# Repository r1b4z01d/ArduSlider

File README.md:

*ArduSlider
** Arduino:
*** API:
The arduino expects each api call to consist of a letter (flag), set of numbers and a charige return. Example: B1000/n
In Flags: 
	T: Length of session in milliseconds
		T60000/n
	S: Sutter speed in milliseconds 
		S1000/n
	B: Length of time the cammera takes to save the image and clear it's buffer in milliseconds.
		B3000/n
	D: Distance of travel for the session in mm
		D1000/n
	R: Boolen trigger to start/stop the session.
		R1/n
	A: Request a full refresh of all parameters
		A/n 

Out:

  sendData("T",String(msOfCapture));
  sendData("P",String(photo));
  sendData("C",String(numPhotos));
  sendData("R",String(isRunning));
  sendData("S",String(shutterSpeed));
  sendData("B",String(bufferClear));
  sendData("D",String(mmOfTravel));
  sendData("L",String(totalSteps));

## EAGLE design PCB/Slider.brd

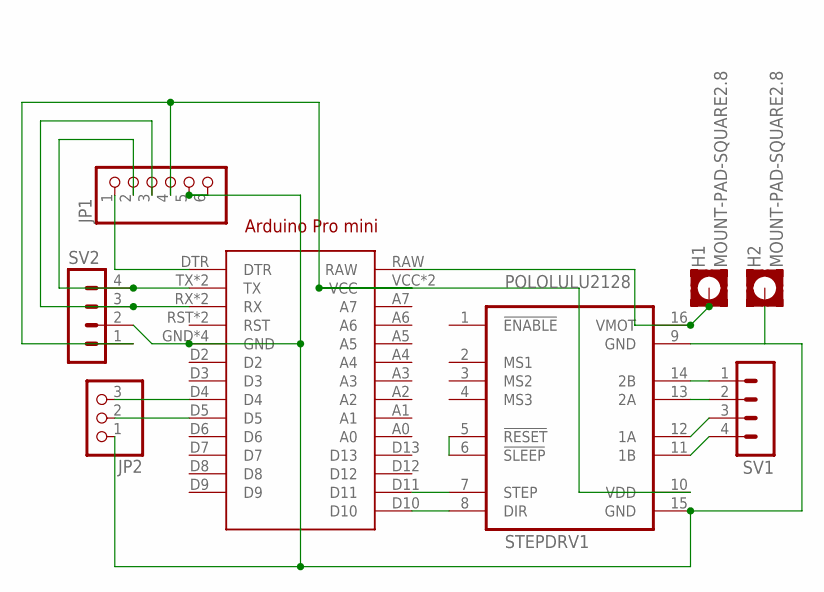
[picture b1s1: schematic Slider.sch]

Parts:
ARDUINO1: ARDUINO_PRO_MINI
H1, H2: MOUNT-PAD-SQUARE2.8; 2,8-PAD-SQUARE
JP1: PINHD-1X6; 1X06
JP2: PINHD-1X3CB; 1X03-CLEANBIG
STEPDRV1: POLOLULU2128
SV1, SV2: MA04-1

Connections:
unnamed: ARDUINO1.D11, STEPDRV1.7 (STEP)
unnamed: ARDUINO1.D10, STEPDRV1.8 (DIR)
unnamed: STEPDRV1.5 (!RESET), STEPDRV1.6 (!SLEEP)
unnamed: STEPDRV1.11 (1B), SV1.4
unnamed: STEPDRV1.12 (1A), SV1.3
unnamed: STEPDRV1.13 (2A), SV1.2
unnamed: STEPDRV1.14 (2B), SV1.1
unnamed: ARDUINO1.RAW, H1.B2,8, STEPDRV1.16 (VMOT)
unnamed: ARDUINO1.VCC, ARDUINO1.VCC@1 (VCC), JP1.4, STEPDRV1.10 (VDD), SV2.1
unnamed: ARDUINO1.GND, ARDUINO1.GND@1 (GND), ARDUINO1.GND@2 (GND), ARDUINO1.GND@3 (GND), H2.B2,8, JP1.5, JP1.6, JP2.1, STEPDRV1.9 (GND), STEPDRV1.15 (GND), SV2.2
unnamed: ARDUINO1.DTR, JP1.1
unnamed: ARDUINO1.RX, ARDUINO1.RX@1 (RX), JP1.3, SV2.3
unnamed: ARDUINO1.TX, ARDUINO1.TX@1 (TX), JP1.2, SV2.4
unnamed: ARDUINO1.D4, JP2.3
unnamed: ARDUINO1.D5, JP2.2

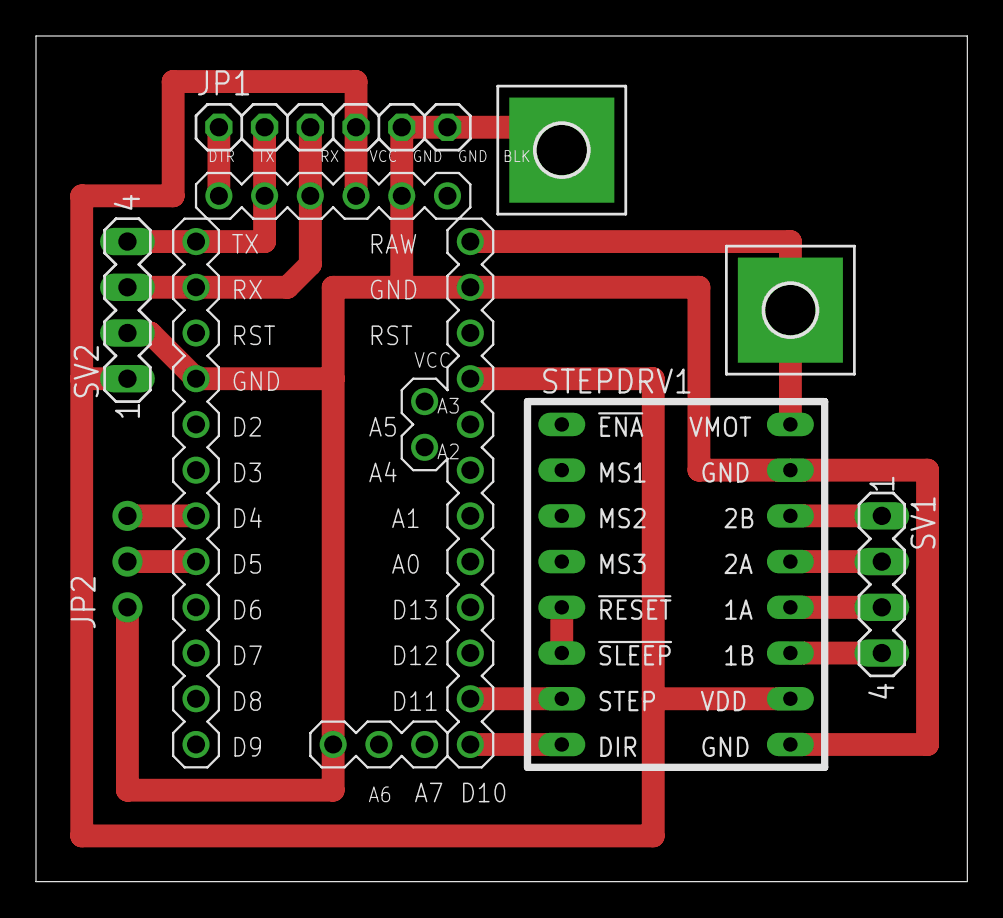
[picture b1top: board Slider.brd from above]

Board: 2 copper layers, 51.7 x 47.0 mm, 8 parts (0 on the bottom side), 15 nets.

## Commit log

2018-08-19 WIP 1st test print
2018-08-19 folders
2018-08-19 PCB, Android & Arduino Code
2018-08-20 thickened motor mount and lowered base
2018-08-20 left & right plus improvements
2018-08-22 never forget to clear the buffer
2018-08-29 started readme and app work
2018-10-31 latest changes
2020-07-10 rename
2020-07-16 Updating name of app, placement of fields and added labels.
